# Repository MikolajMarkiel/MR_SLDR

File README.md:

# WARNING!

The project is in build stage. Missing documentation and functionalities will be added in time.

# Overview

The MR_SLDR is a project of remote controlled slider for camera. It will be controlled by Bluetooth Low Energy protocol. The main library source for this project is Zephyr OS.

# How to run

# Software description

## Web_bluetooth

## timer

Due to problems with flexibility occurence of threads in zephyr (minimal period step is 100us) I've decided to leave control of stepper motor up to hardware timer peripheral. Unfortunately right now esp32 timer drivers are dedicated only for counters that lose synchronization after overflow of counted ticks. Because of that I had to add extra modification to counter_esp32_tmr.c file (this file is a driver to handle every action of timer after setting devicetree &timerX status = "okay"). The modification allow us to decide that counter will autoreset after getting alarm or won't. It doesn't harm any project that use old driver, because for this to work user has to add extra `COUNTER_AUTORESET` config to Kconfig file. I've included new counter_esp32_tmr.c file in bin/ directory. The path for replacement is `../zephyrproject/zephyr/drivers/counter/counter_esp32_tmr.c`

## Distance_meter

# Hardware description

## Power section

The main supply for the board is +5V microUSB port. It supplies two DC-DC converters: step-up to +12V and step-down to +3,3V. The +12 DC voltage is needed for charging alternative power supply based on 3 li-ion cells driven by BMS3451 BMS. If there is no USB cable connected, then step-down converter is supplied by +12V instead. There is an external switch that enables step-down converter. If it is disabled, then every peripheral would be powered down except stepper motor driver which would go into sleep mode instead. Connecting USB cable with switch turned off allow charging batteries without turning on the device.
Voltage level of cell block is continually checked by ADC, and the feedback information is given to user via BLE.

## CPU & programming

An ESP32 module has been chosen as a CPU for the device. It has been because of his low cost and support for bluetooth communication and zephyr OS. There are two ways to communicate PC with CPU: via CP2102 USB to UART bridge module connected to micro USB and JTAG connector. Both allow to program flash memory. Additionally the bridge provides serial communication with PC and JTAG give possibility to debug software.

## Stepper motor driver

DRV8825 module has been used as an output driver for stepper motor. It provides easy interface because of it's STEP/DIR functionality. For more information please refer to datasheet of module.

## Distance meter

For checking actual position of camera even after power off the laser distance meter VL53LXX module is connected to CPU by I2C interface. Because it is needed to connect module directly at path of moving camera, then the module has been removed from the main hardware PCB and case. For more information please refer to datasheet of module.

## Camera control blocks

There are also two isolated switches for example for activating remote control of camera or other these types activities. They are designed with use of single channel transoptors PC817.

## EEPROM

The board provides also external EEPROM (M93C76C module) for saving user data of slider settings. It communicates with CPU via SPI interface.

## Mechanicals

The board has been designed for Z57J universal case (https://www.kradex.com.pl/product/enclosures_hermetically_sealed/z57j_ps?lang=en) but it is also possible to print something similar. By now there is no need to provide additional 3D models of case.

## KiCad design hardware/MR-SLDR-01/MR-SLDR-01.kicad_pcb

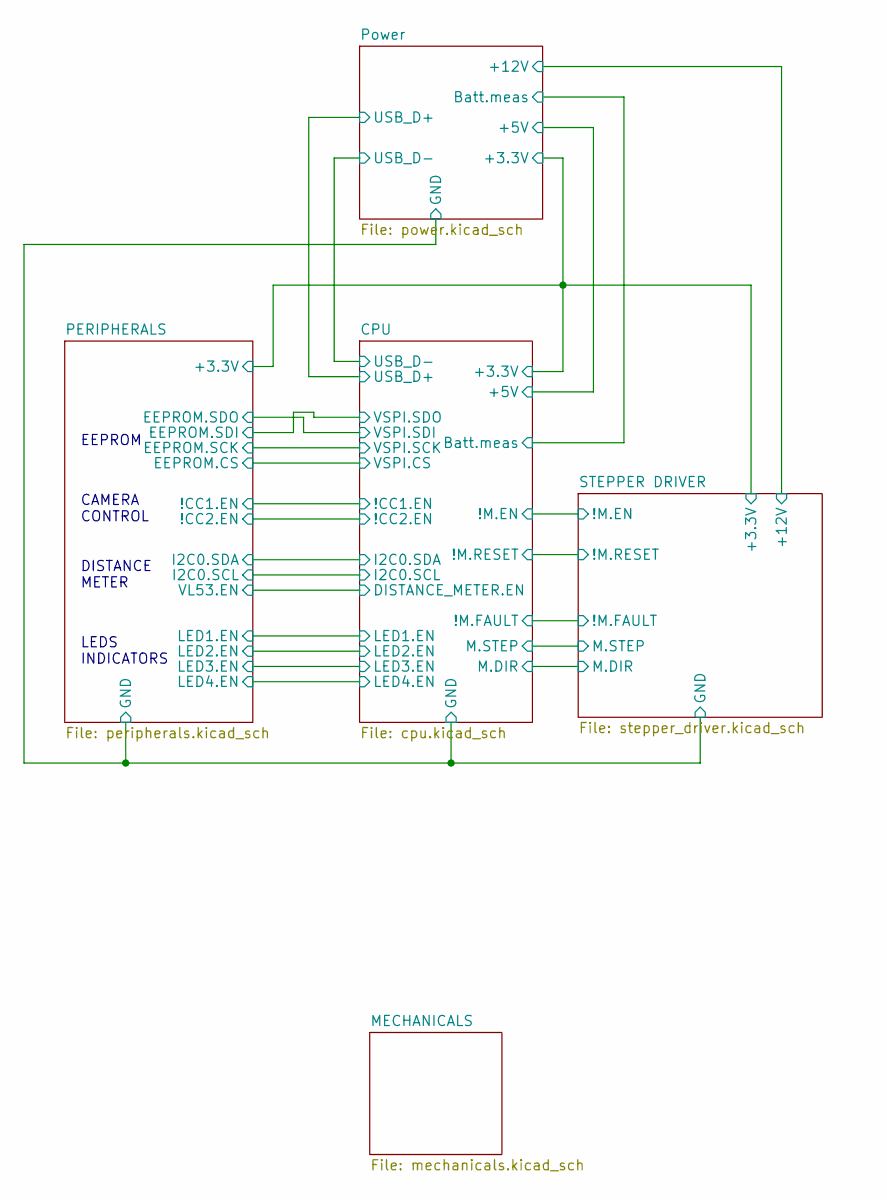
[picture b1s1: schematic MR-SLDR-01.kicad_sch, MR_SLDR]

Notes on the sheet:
LEDS INDICATORS
DISTANCE METER
CAMERA CONTROL
EEPROM

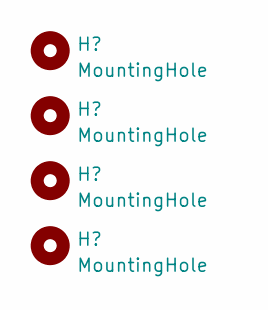
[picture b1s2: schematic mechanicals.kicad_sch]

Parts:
H1, H2, H3, H4: MountingHole; MountingHole_3.2mm_M3

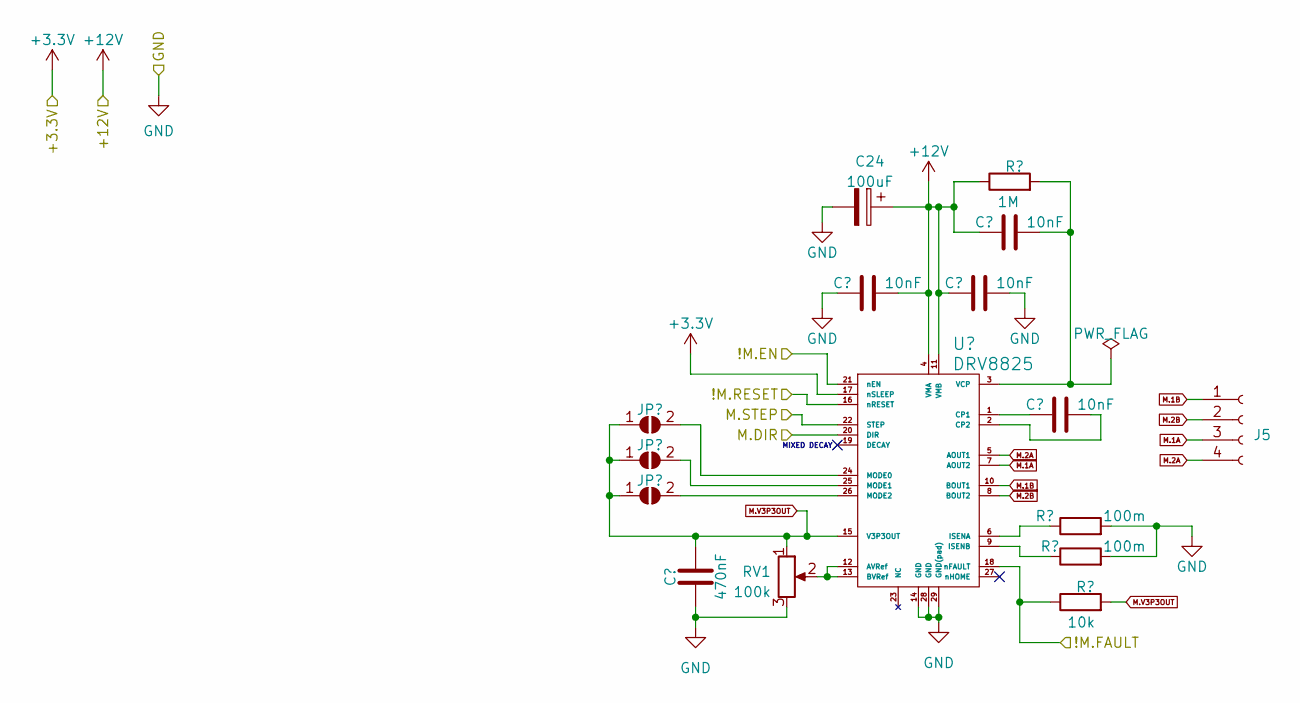
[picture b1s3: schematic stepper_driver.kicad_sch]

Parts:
C23: 470nF; C_0805_2012Metric_Pad1.18x1.45mm_HandSolder
C24: 100uF; CP_Radial_D8.0mm_P3.80mm
C25, C26, C27, C28: 10nF; C_0805_2012Metric_Pad1.18x1.45mm_HandSolder
J5: Conn_01x04_Socket; Molex_KK-254_AE-6410-04A_1x04_P2.54mm_Vertical
JP3, JP4, JP5: SolderJumper_2_Open; SolderJumper-2_P1.3mm_Open_RoundedPad1.0x1.5mm
R35: 1M; R_0805_2012Metric_Pad1.20x1.40mm_HandSolder
R36, R37: 100m; R_1206_3216Metric_Pad1.30x1.75mm_HandSolder
R38: 10k; R_0805_2012Metric_Pad1.20x1.40mm_HandSolder
RV1: 100k; Potentiometer_Bourns_3296W_Vertical
U6: DRV8825; HTSSOP-28-1EP_4.4x9.7mm_P0.65mm_EP3.4x9.5mm_ThermalVias

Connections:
+3.3V: U6.17 (nSLEEP); also elsewhere on the board
+12V: C24.1, C25.2, C26.1, C27.1, R35.1, U6.4 (VMA), U6.11 (VMB); also elsewhere on the board
/CPU/!M.EN: U6.21 (nEN); also elsewhere on the board
/CPU/!M.FAULT: R38.1, U6.18 (nFAULT); also elsewhere on the board
/CPU/!M.RESET: U6.16 (nRESET); also elsewhere on the board
/CPU/M.DIR: U6.20 (DIR); also elsewhere on the board
/CPU/M.STEP: U6.22 (STEP); also elsewhere on the board
GND: C23.1, C24.2, C25.1, C26.2, R36.2, R37.2, RV1.3, U6.14 (GND), U6.28 (GND), U6.29 (GND(pad)); also elsewhere on the board
M.1A: J5.3, U6.7 (AOUT2)
M.1B: J5.1, U6.10 (BOUT1)
M.2A: J5.4, U6.5 (AOUT1)
M.2B: J5.2, U6.8 (BOUT2)
M.V3P3OUT: C23.2, JP3.1 (A), JP4.1 (A), JP5.1 (A), R38.2, RV1.1, U6.15 (V3P3OUT)
unnamed: JP3.2 (B), U6.24 (MODE0)
unnamed: JP4.2 (B), U6.25 (MODE1)
unnamed: JP5.2 (B), U6.26 (MODE2)
unnamed: RV1.2, U6.12 (AVRef), U6.13 (BVRef)
unnamed: C28.1, U6.1 (CP1)
unnamed: C28.2, U6.2 (CP2)
unnamed: R36.1, U6.6 (ISENA)
unnamed: R37.1, U6.9 (ISENB)
unnamed: C27.2, R35.2, U6.3 (VCP)

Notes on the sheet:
MIXED DECAY

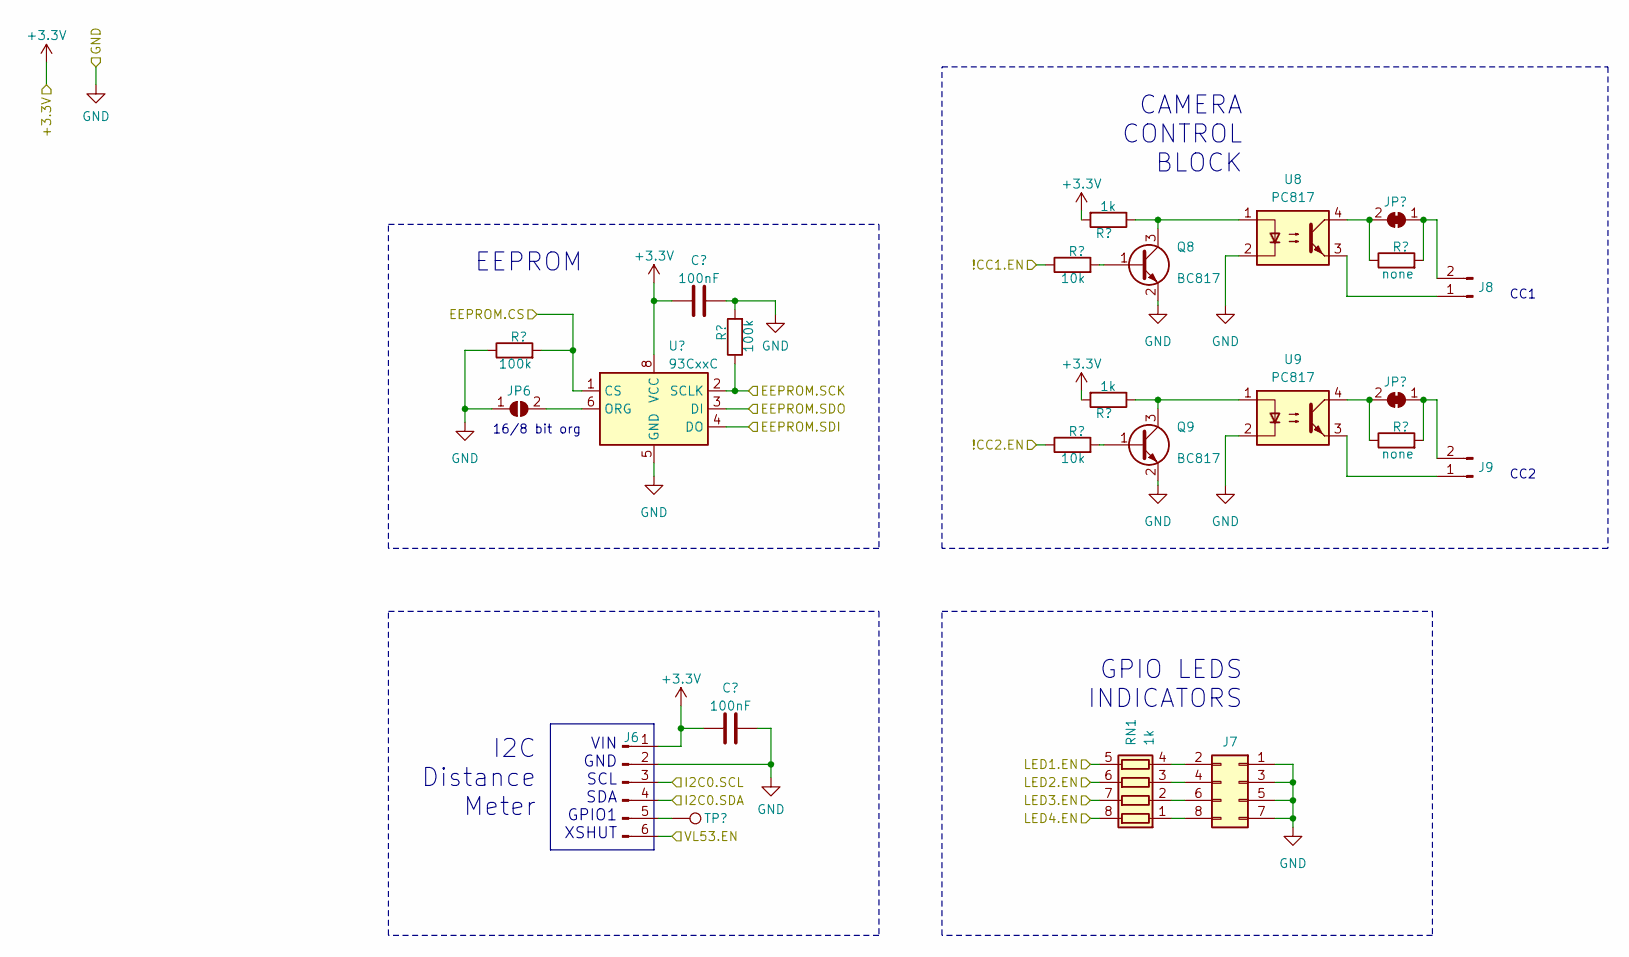
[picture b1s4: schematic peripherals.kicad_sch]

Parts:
C29, C30: 100nF; C_0805_2012Metric_Pad1.18x1.45mm_HandSolder
J6: Conn_01x06_Pin; Molex_KK-254_AE-6410-06A_1x06_P2.54mm_Vertical
J7: Conn_02x04_Odd_Even; PinSocket_2x04_P2.54mm_Vertical
J8, J9: Conn_01x02_Pin; Molex_SL_171971-0002_1x02_P2.54mm_Vertical
JP6: SolderJumper_2_Open; SolderJumper-2_P1.3mm_Open_RoundedPad1.0x1.5mm
JP7, JP8: SolderJumper_2_Bridged; SolderJumper-2_P1.3mm_Bridged_RoundedPad1.0x1.5mm
Q8, Q9: BC817; SOT-23
R39, R40: 100k; R_0805_2012Metric_Pad1.20x1.40mm_HandSolder
R41, R42: 10k; R_0805_2012Metric_Pad1.20x1.40mm_HandSolder
R43, R44: 1k; R_0805_2012Metric_Pad1.20x1.40mm_HandSolder
R45, R46: none; R_0805_2012Metric_Pad1.20x1.40mm_HandSolder
RN1: 1k; R_Array_Convex_4x1206
TP8: TestPoint; TestPoint_THTPad_1.0x1.0mm_Drill0.5mm
U7: 93CxxC; SO-8_3.9x4.9mm_P1.27mm
U8, U9: PC817; DIP-4_W7.62mm

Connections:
+3.3V: C29.2, C30.2, J6.1, R43.2, R44.2, U7.8 (VCC); also elsewhere on the board
/CPU/!CC1.EN: R41.1; also elsewhere on the board
/CPU/!CC2.EN: R42.1; also elsewhere on the board
/CPU/DISTANCE_METER.EN: J6.6; also elsewhere on the board
/CPU/I2C0.SCL: J6.3; also elsewhere on the board
/CPU/I2C0.SDA: J6.4; also elsewhere on the board
/CPU/LED1.EN: RN1.5 (R4.2); also elsewhere on the board
/CPU/LED2.EN: RN1.6 (R3.2); also elsewhere on the board
/CPU/LED3.EN: RN1.7 (R2.2); also elsewhere on the board
/CPU/LED4.EN: RN1.8 (R1.2); also elsewhere on the board
/CPU/VSPI.CS: R39.2, U7.1 (CS); also elsewhere on the board
/CPU/VSPI.SCK: R40.1, U7.2 (SCLK); also elsewhere on the board
/CPU/VSPI.SDI: U7.3 (DI); also elsewhere on the board
/CPU/VSPI.SDO: U7.4 (DO); also elsewhere on the board
GND: C29.1, C30.1, J6.2, J7.1, J7.3, J7.5, J7.7, JP6.1 (A), Q8.2 (E), Q9.2 (E), R39.1, R40.2, U7.5 (GND), U8.2, U9.2; also elsewhere on the board
unnamed: J6.5, TP8.1
unnamed: J7.2, RN1.4 (R4.1)
unnamed: J7.4, RN1.3 (R3.1)
unnamed: J7.6, RN1.2 (R2.1)
unnamed: J7.8, RN1.1 (R1.1)
unnamed: J8.1, U8.3
unnamed: J9.1, U9.3
unnamed: J9.2, JP8.1 (A), R46.2
unnamed: JP6.2 (B), U7.6 (ORG)
unnamed: JP8.2 (B), R46.1, U9.4
unnamed: Q8.1 (B), R41.2
unnamed: Q8.3 (C), R43.1, U8.1
unnamed: Q9.1 (B), R42.2
unnamed: Q9.3 (C), R44.1, U9.1

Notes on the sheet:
CC1
GPIO LEDS INDICATORS
CC2
16/8 bit org
VIN GND SCL SDA GPIO1 XSHUT
I2C Distance Meter
CAMERA CONTROL BLOCK
EEPROM

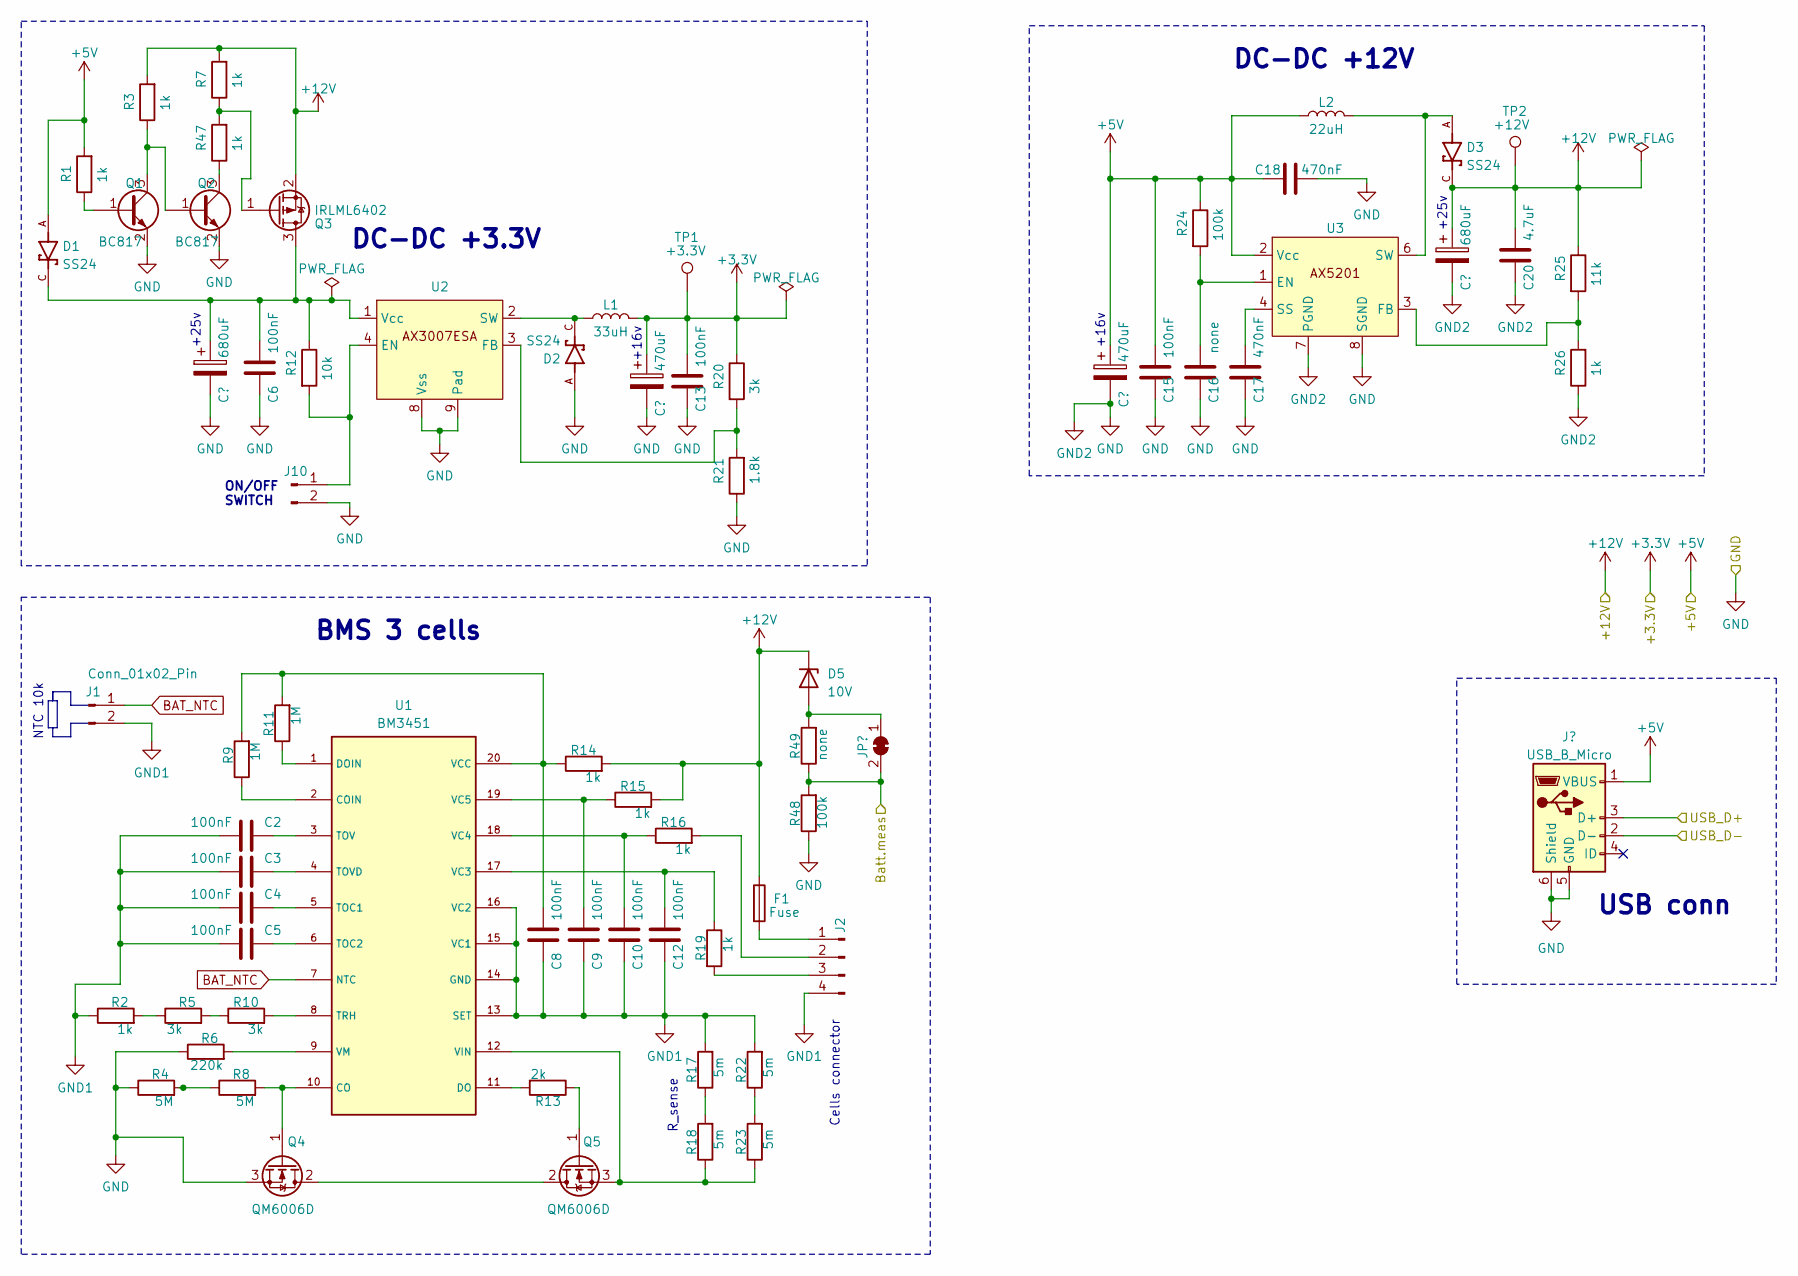
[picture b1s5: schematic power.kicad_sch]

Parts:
C1, C19: 680uF; CP_Radial_D10.0mm_P5.00mm
C2, C3, C4, C5, C6, C8, C9, C10, C12, C13, C15: 100nF; C_0805_2012Metric_Pad1.18x1.45mm_HandSolder
C11, C14: 470uF; CP_Radial_D8.0mm_P3.80mm
C16: none; C_0805_2012Metric_Pad1.18x1.45mm_HandSolder
C17, C18: 470nF; C_0805_2012Metric_Pad1.18x1.45mm_HandSolder
C20: 4.7uF; C_1206_3216Metric_Pad1.33x1.80mm_HandSolder
D1, D2, D3: SS24; DIOM5336X265N; PARTREV 1.1.2
D5: 10V; D_MiniMELF
F1: Fuse; Fuse_1206_3216Metric_Pad1.42x1.75mm_HandSolder
J1, J10: Conn_01x02_Pin; Molex_SL_171971-0002_1x02_P2.54mm_Vertical
J2: Conn_01x04_Pin; Molex_KK-254_AE-6410-04A_1x04_P2.54mm_Vertical
J3: USB_B_Micro; USB_Micro-B_Amphenol_10118194_Horizontal
JP7: SolderJumper_2_Bridged; SolderJumper-2_P1.3mm_Bridged_RoundedPad1.0x1.5mm
L1: 33uH; L_12x12mm_H8mm
L2: 22uH; L_TDK_VLF10040
Q1, Q2: BC817; SOT-23
Q3: IRLML6402; SOT-23
Q4, Q5: QM6006D; TO-252-2
R1, R2, R3, R7, R14, R15, R16, R19, R26, R47: 1k; R_0805_2012Metric_Pad1.20x1.40mm_HandSolder
R4, R8: 5M; R_0805_2012Metric_Pad1.20x1.40mm_HandSolder
R5, R10, R20: 3k; R_0805_2012Metric_Pad1.20x1.40mm_HandSolder
R6: 220k; R_0805_2012Metric_Pad1.20x1.40mm_HandSolder
R9, R11: 1M; R_0805_2012Metric_Pad1.20x1.40mm_HandSolder
R12: 10k; R_0805_2012Metric_Pad1.20x1.40mm_HandSolder
R13: 2k; R_0805_2012Metric_Pad1.20x1.40mm_HandSolder
R17, R18, R22, R23: 5m; R_2512_6332Metric_Pad1.40x3.35mm_HandSolder
R21: 1.8k; R_0805_2012Metric_Pad1.20x1.40mm_HandSolder
R24, R48: 100k; R_0805_2012Metric_Pad1.20x1.40mm_HandSolder
R25: 11k; R_0805_2012Metric_Pad1.20x1.40mm_HandSolder
R49: none; R_0805_2012Metric_Pad1.20x1.40mm_HandSolder
TP1: +3.3V; TestPoint_THTPad_1.0x1.0mm_Drill0.5mm
TP2: +12V; TestPoint_THTPad_1.0x1.0mm_Drill0.5mm
U1: BM3451; TSSOP-20_4.4x6.5mm_P0.65mm
U2, U3: SOIC-8-1EP_3.9x4.9mm_P1.27mm_EP2.29x3mm

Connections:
+3.3V: C11.1, C13.1, L1.2, R20.1, TP1.1; also elsewhere on the board
+5V: C14.1, C15.1, C18.1, D1.A, J3.1 (VBUS), L2.1, R1.2, R24.1, U3.2 (Vcc); also elsewhere on the board
+12V: C19.1, C20.1, D3.C, D5.1 (K), F1.1, Q3.2 (S), R3.2, R7.2, R14.2, R15.2, R25.1, TP2.1; also elsewhere on the board
/CPU/USB_D+: J3.3 (D+); also elsewhere on the board
/CPU/USB_D-: J3.2 (D-); also elsewhere on the board
BAT_NTC: J1.1, U1.7 (NTC)
GND: C1.2, C6.2, C11.2, C13.2, C14.2, C15.2, C16.2, C17.2, C18.2, C19.2, C20.2, D2.A, J3.5 (GND), J3.6 (Shield), J10.2, Q1.2 (E), Q2.2 (E), Q4.3 (S), R4.1, R6.1, R21.1, R26.1, R48.1, U2.5 (Vss), U2.6 (Vss), U2.7 (Vss), U2.8 (Vss), U2.9 (Pad), U3.7 (PGND), U3.8 (SGND); also elsewhere on the board
GND1: C2.1, C3.1, C4.1, C5.1, C8.2, C9.2, C10.2, C12.2, J1.2, J2.4, R2.1, R17.2, R22.2, U1.13 (SET), U1.14 (GND), U1.15 (VC1), U1.16 (VC2)
unnamed: D3.A, L2.2, U3.5 (SW), U3.6 (SW), U3.9 (Pad)
unnamed: F1.2, J2.1
unnamed: J2.2, R16.2
unnamed: J2.3, R19.2
unnamed: J10.1, R12.2, U2.4 (EN)
unnamed: Q1.1 (B), R1.1
unnamed: Q1.3 (C), Q2.1 (B), R3.1
unnamed: Q2.3 (C), R47.1
unnamed: C1.1, C6.1, D1.C, Q3.3 (D), R12.1, U2.1 (Vcc)
unnamed: Q3.1 (G), R7.1, R47.2
unnamed: Q4.2 (D), Q5.2 (D)
unnamed: Q4.1 (G), R8.2, U1.10 (CO)
unnamed: Q5.1 (G), R13.1
unnamed: Q5.3 (S), R18.1, R23.1, U1.12 (VIN)
unnamed: R2.2, R5.1
unnamed: R4.2, R8.1
unnamed: R5.2, R10.1
unnamed: R17.1, R18.2
unnamed: R22.1, R23.2
unnamed: R9.1, U1.2 (COIN)
unnamed: R13.2, U1.11 (DO)
unnamed: R11.1, U1.1 (DOIN)
unnamed: C4.2, U1.5 (TOC1)
unnamed: C5.2, U1.6 (TOC2)
unnamed: C2.2, U1.3 (TOV)
unnamed: C3.2, U1.4 (TOVD)
unnamed: R10.2, U1.8 (TRH)
unnamed: C12.1, R19.1, U1.17 (VC3)
unnamed: C10.1, R16.1, U1.18 (VC4)
unnamed: C9.1, R15.1, U1.19 (VC5)
unnamed: C8.1, R9.2, R11.2, R14.1, U1.20 (VCC)
unnamed: R6.2, U1.9 (VM)
unnamed: R20.2, R21.2, U2.3 (FB)
unnamed: D2.C, L1.1, U2.2 (SW)
unnamed: C16.1, R24.2, U3.1 (EN)
unnamed: R25.2, R26.2, U3.3 (FB)
unnamed: C17.1, U3.4 (SS)

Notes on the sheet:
USB conn
+25v
R_sense
BMS 3 cells
DC-DC +12V
+16v
ON/OFF SWITCH
NTC 10k
DC-DC +3.3V
Cells connector

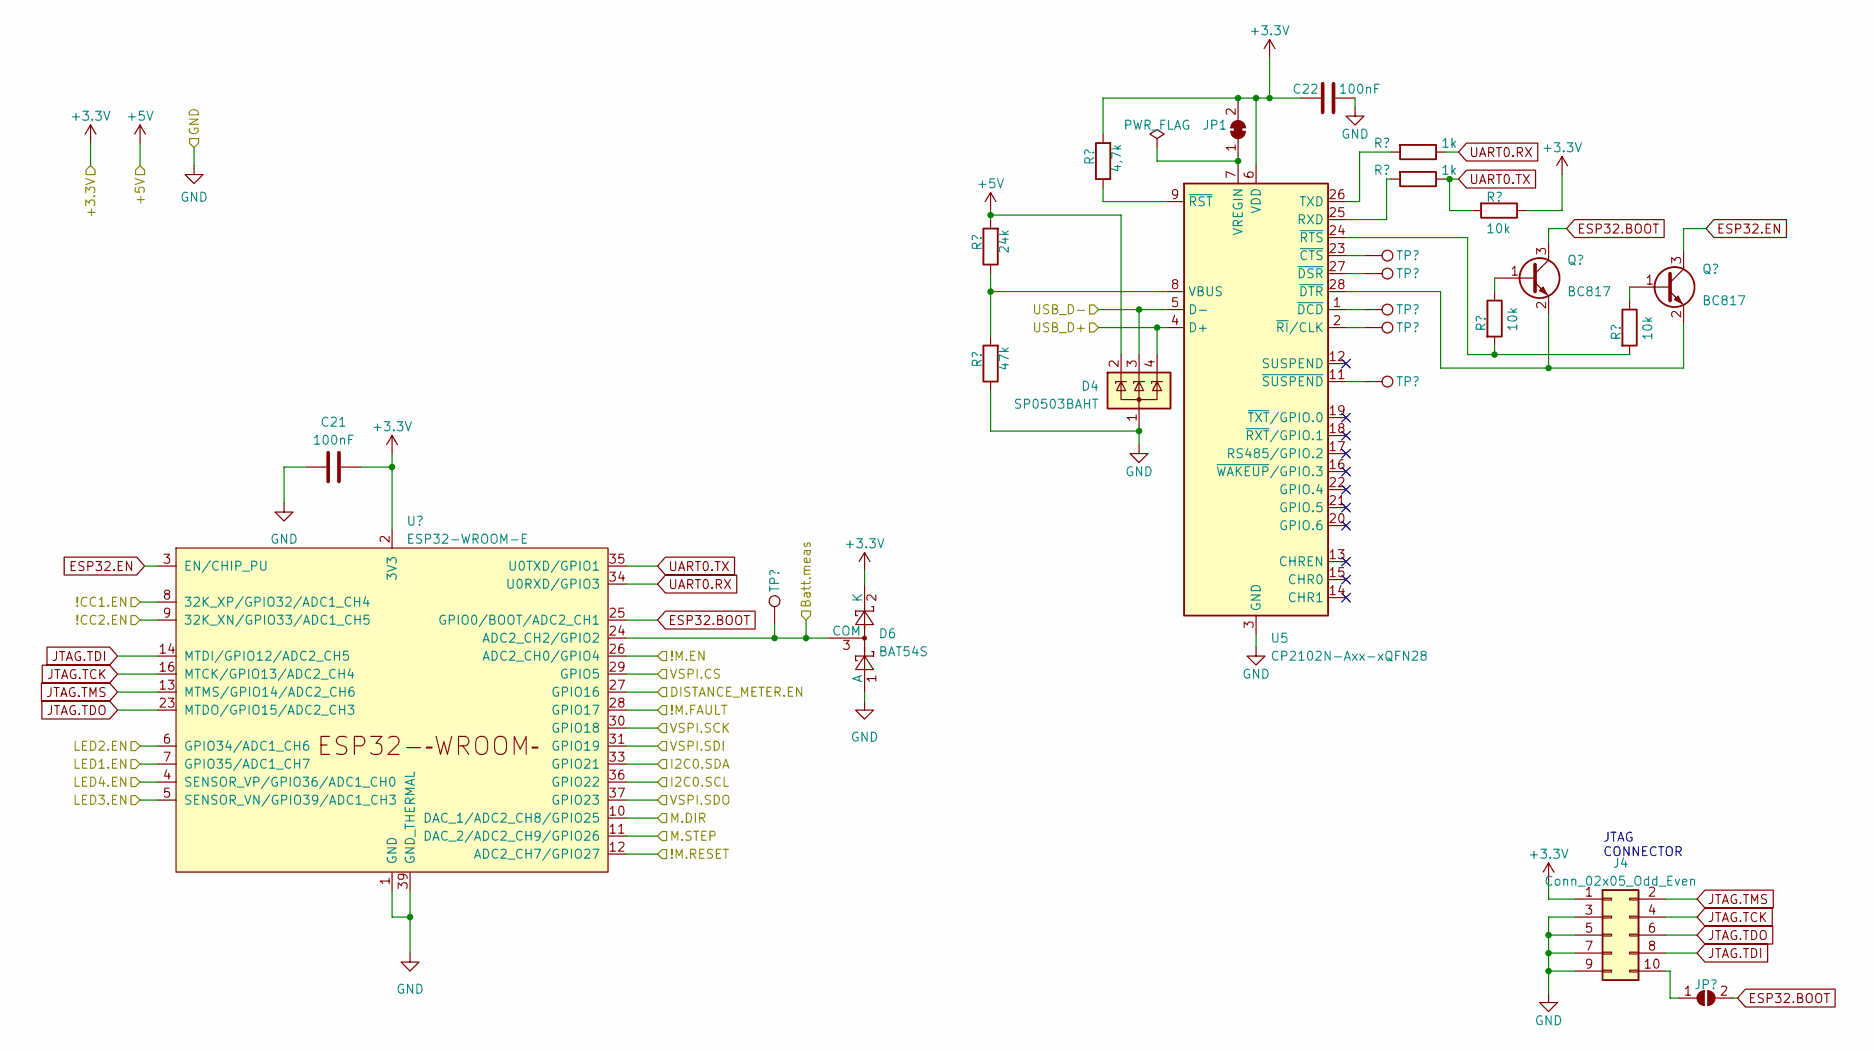
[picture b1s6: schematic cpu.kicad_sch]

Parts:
Batt.meas1: TestPoint; TestPoint_THTPad_1.0x1.0mm_Drill0.5mm
C21, C22: 100nF; C_0805_2012Metric_Pad1.18x1.45mm_HandSolder
D4: SP0503BAHT; SOT-143
D6: BAT54S; SOT-23
J4: Conn_02x05_Odd_Even; PinHeader_2x05_P2.00mm_Vertical
JP1: SolderJumper_2_Bridged; SolderJumper-2_P1.3mm_Bridged_RoundedPad1.0x1.5mm
JP2: SolderJumper_2_Open; SolderJumper-2_P1.3mm_Open_RoundedPad1.0x1.5mm
Q6, Q7: BC817; SOT-23
R27: 24k; R_0805_2012Metric_Pad1.20x1.40mm_HandSolder
R28: 47k; R_0805_2012Metric_Pad1.20x1.40mm_HandSolder
R29: 4,7k; R_0805_2012Metric_Pad1.20x1.40mm_HandSolder
R30, R31: 1k; R_0805_2012Metric_Pad1.20x1.40mm_HandSolder
R32, R33, R34: 10k; R_0805_2012Metric_Pad1.20x1.40mm_HandSolder
TP3, TP4, TP5, TP6, TP7: TestPoint; TestPoint_THTPad_1.0x1.0mm_Drill0.5mm
U4: ESP32-WROOM-E; ESP32-WROOM-32E
U5: CP2102N-Axx-xQFN28; QFN-28-1EP_5x5mm_P0.5mm_EP3.35x3.35mm

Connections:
+3.3V: C21.2, C22.1, D6.2 (K), J4.1, JP1.2 (B), R29.2, R33.1, U4.2 (3V3), U5.6 (VDD); also elsewhere on the board
+5V: D4.2 (K), R27.2; also elsewhere on the board
/CPU/!CC1.EN: U4.8 (32K_XP/GPIO32/ADC1_CH4); also elsewhere on the board
/CPU/!CC2.EN: U4.9 (32K_XN/GPIO33/ADC1_CH5); also elsewhere on the board
/CPU/!M.EN: U4.26 (ADC2_CH0/GPIO4); also elsewhere on the board
/CPU/!M.FAULT: U4.28 (GPIO17); also elsewhere on the board
/CPU/!M.RESET: U4.12 (ADC2_CH7/GPIO27); also elsewhere on the board
/CPU/DISTANCE_METER.EN: U4.27 (GPIO16); also elsewhere on the board
/CPU/I2C0.SCL: U4.36 (GPIO22); also elsewhere on the board
/CPU/I2C0.SDA: U4.33 (GPIO21); also elsewhere on the board
/CPU/LED1.EN: U4.7 (GPIO35/ADC1_CH7); also elsewhere on the board
/CPU/LED2.EN: U4.6 (GPIO34/ADC1_CH6); also elsewhere on the board
/CPU/LED3.EN: U4.5 (SENSOR_VN/GPIO39/ADC1_CH3); also elsewhere on the board
/CPU/LED4.EN: U4.4 (SENSOR_VP/GPIO36/ADC1_CH0); also elsewhere on the board
/CPU/M.DIR: U4.10 (DAC_1/ADC2_CH8/GPIO25); also elsewhere on the board
/CPU/M.STEP: U4.11 (DAC_2/ADC2_CH9/GPIO26); also elsewhere on the board
/CPU/USB_D+: D4.4 (K), U5.4 (D+); also elsewhere on the board
/CPU/USB_D-: D4.3 (K), U5.5 (D-); also elsewhere on the board
/CPU/VSPI.CS: U4.29 (GPIO5); also elsewhere on the board
/CPU/VSPI.SCK: U4.30 (GPIO18); also elsewhere on the board
/CPU/VSPI.SDI: U4.31 (GPIO19); also elsewhere on the board
/CPU/VSPI.SDO: U4.37 (GPIO23); also elsewhere on the board
ESP32.BOOT: JP2.2 (B), Q6.3 (C), U4.25 (GPIO0/BOOT/ADC2_CH1)
ESP32.EN: Q7.3 (C), U4.3 (EN/CHIP_PU)
GND: C21.1, C22.2, D4.1 (A), D6.1 (A), J4.3, J4.5, J4.7, J4.9, R28.1, U4.1 (GND), U4.15 (GND), U4.38 (GND), U4.39 (GND_THERMAL), U5.3 (GND), U5.29 (GND); also elsewhere on the board
JTAG.TCK: J4.4, U4.16 (MTCK/GPIO13/ADC2_CH4)
JTAG.TDI: J4.8, U4.14 (MTDI/GPIO12/ADC2_CH5)
JTAG.TDO: J4.6, U4.23 (MTDO/GPIO15/ADC2_CH3)
JTAG.TMS: J4.2, U4.13 (MTMS/GPIO14/ADC2_CH6)
unnamed: J4.10, JP2.1 (A)
unnamed: JP1.1 (A), U5.7 (VREGIN)
unnamed: Q6.1 (B), R32.1
unnamed: Q6.2 (E), Q7.2 (E), U5.28 (~DTR)
unnamed: Q7.1 (B), R34.1
unnamed: R31.2, U5.25 (RXD)
unnamed: R30.2, U5.26 (TXD)
unnamed: R27.1, R28.2, U5.8 (VBUS)
unnamed: TP3.1, U5.23 (~CTS)
unnamed: TP5.1, U5.1 (~DCD)
unnamed: TP4.1, U5.27 (~DSR)
unnamed: TP6.1, U5.2 (~RI/CLK)
unnamed: R29.1, U5.9 (~RST)
unnamed: R32.2, R34.2, U5.24 (~RTS)
unnamed: TP7.1, U5.11 (~SUSPEND)
UART0.RX: R30.1, U4.34 (U0RXD/GPIO3)
UART0.TX: R31.1, R33.2, U4.35 (U0TXD/GPIO1)

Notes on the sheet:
JTAG CONNECTOR

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
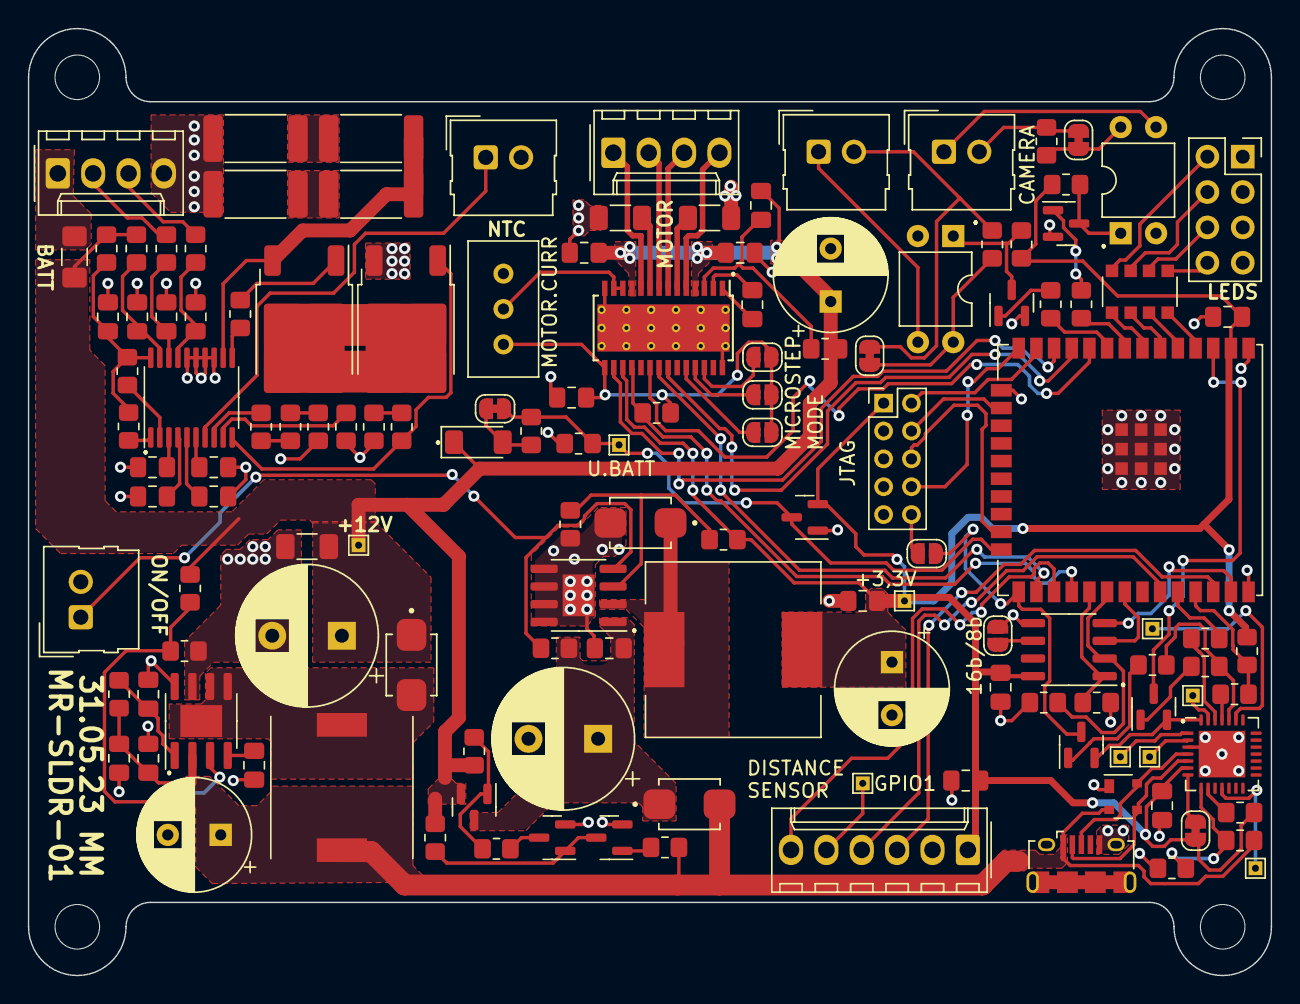
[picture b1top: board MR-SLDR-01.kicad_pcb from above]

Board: 2 copper layers, 89.3 x 68.0 mm, 139 parts (0 on the bottom side), 118 nets.

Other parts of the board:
JP9: SolderJumper_2_Bridged; SolderJumper-2_P1.3mm_Bridged_RoundedPad1.0x1.5mm

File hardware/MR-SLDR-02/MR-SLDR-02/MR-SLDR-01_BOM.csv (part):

"Source:","/home/mikolaj/projects/MR-SLDR/hardware/MR-SLDR-01/MR-SLDR-01.kicad_sch"
"Date:","pią, 2 cze 2023, 03:15:36"
"Tool:","Eeschema 7.0.2-6a45011f42~172~ubuntu22.04.1"
"Generator:","/usr/share/kicad/plugins/bom_csv_grouped_by_value.py"
"Component Count:","139"

"Collated Components:"

"Item","Qty","Reference(s)","Value","LibPart","Footprint","Datasheet","DNP","MANUFACTURER","MAXIMUM_PACKAGE_HEIGHT","PARTREV","STANDARD","Sim.Device","Sim.Pins","Sim.Type"
"1","7","Batt.meas1, TP3, TP4, TP5, TP6, TP7, TP8","TestPoint","Connector:TestPoint","TestPoint:TestPoint_THTPad_1.0x1.0mm_Drill0.5mm","~","","","","","","","",""
"2","2","C1, C19","680uF","Device:C_Polarized","Capacitor_THT:CP_Radial_D10.0mm_P5.00mm","~","","","","","","","",""
"3","15","C2, C3, C4, C5, C6, C8, C9, C10, C12, C13, C15, C21, C22, C29, C30","100nF","Device:C","Capacitor_SMD:C_0805_2012Metric_Pad1.18x1.45mm_HandSolder","~","","","","","","","",""
"4","2","C11, C14","470uF","Device:C_Polarized","Capacitor_THT:CP_Radial_D8.0mm_P3.80mm","~","","","","","","","",""
"5","1","C16","none","Device:C","Capacitor_SMD:C_0805_2012Metric_Pad1.18x1.45mm_HandSolder","~","","","","","","","",""
"6","3","C17, C18, C23","470nF","Device:C","Capacitor_SMD:C_0805_2012Metric_Pad1.18x1.45mm_HandSolder","~","","","","","","","",""
"7","1","C20","4.7uF","Device:C","Capacitor_SMD:C_1206_3216Metric_Pad1.33x1.80mm_HandSolder","~","","","","","","","",""
"8","1","C24","100uF","Device:C_Polarized","Capacitor_THT:CP_Radial_D8.0mm_P3.80mm","~","","","","","","","",""
"9","4","C25, C26, C27, C28","10nF","Device:C","Capacitor_SMD:C_0805_2012Metric_Pad1.18x1.45mm_HandSolder","~","","","","","","","",""
"10","3","D1, D2, D3","SS24","SS24:SS24","bin:DIOM5336X265N","","","ON Semiconductor","2.65 mm","1.1.2","IPC 7351B","","",""
"11","1","D4","SP0503BAHT","Power_Protection:SP0503BAHT","Package_TO_SOT_SMD:SOT-143","http://www.littelfuse.com/~/media/files/littelfuse/technical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","","","","","","","",""
"12","1","D5","10V","Device:D_Zener","Diode_SMD:D_MiniMELF","~","","","","","","","",""
"13","1","D6","BAT54S","Diode:BAT54S","Package_TO_SOT_SMD:SOT-23","https://www.diodes.com/assets/Datasheets/ds11005.pdf","","","","","","","",""
"14","1","F1","Fuse","Device:Fuse","Fuse:Fuse_1206_3216Metric_Pad1.42x1.75mm_HandSolder","~","","","","","","","",""
"15","4","H1, H2, H3, H4","MountingHole","Mechanical:MountingHole","MountingHole:MountingHole_3.2mm_M3","~","","","","","","","",""
"16","4","J1, J8, J9, J10","Conn_01x02_Pin","Connector:Conn_01x02_Pin","Connector_Molex:Molex_SL_171971-0002_1x02_P2.54mm_Vertical","~","","","","","","","",""
"17","1","J2","Conn_01x04_Pin","Connector:Conn_01x04_Pin","Connector_Molex:Molex_KK-254_AE-6410-04A_1x04_P2.54mm_Vertical","~","","","","","","","",""
"18","1","J3","USB_B_Micro","Connector:USB_B_Micro","Connector_USB:USB_Micro-B_Amphenol_10118194_Horizontal","~","","","","","","","",""
"19","1","J4","Conn_02x05_Odd_Even","Connector_Generic:Conn_02x05_Odd_Even","Connector_PinHeader_2.00mm:PinHeader_2x05_P2.00mm_Vertical","~","","","","","","","",""
"20","1","J5","Conn_01x04_Socket","Connector:Conn_01x04_Socket","Connector_Molex:Molex_KK-254_AE-6410-04A_1x04_P2.54mm_Vertical","~","","","","","","","",""
"21","1","J6","Conn_01x06_Pin","Connector:Conn_01x06_Pin","Connector_Molex:Molex_KK-254_AE-6410-06A_1x06_P2.54mm_Vertical","~","","","","","","","",""
"22","1","J7","Conn_02x04_Odd_Even","Connector_Generic:Conn_02x04_Odd_Even","Connector_PinSocket_2.54mm:PinSocket_2x04_P2.54mm_Vertical","~","","","","","","","",""
"23","4","JP1, JP7, JP8, JP9","SolderJumper_2_Bridged","Jumper:SolderJumper_2_Bridged","Jumper:SolderJumper-2_P1.3mm_Bridged_RoundedPad1.0x1.5mm","~","","","","","","","",""
"24","5","JP2, JP3, JP4, JP5, JP6","SolderJumper_2_Open","Jumper:SolderJumper_2_Open","Jumper:SolderJumper-2_P1.3mm_Open_RoundedPad1.0x1.5mm","~","","","","","","","",""
"25","1","L1","33uH","Device:L","Inductor_SMD:L_12x12mm_H8mm","~","","","","","","","",""
"26","1","L2","22uH","Device:L","Inductor_SMD:L_TDK_VLF10040","~","","","","","","","",""
"27","6","Q1, Q2, Q6, Q7, Q8, Q9","BC817","Transistor_BJT:BC817","Package_TO_SOT_SMD:SOT-23","https://www.onsemi.com/pub/Collateral/BC818-D.pdf","","","","","","","",""
"28","1","Q3","IRLML6402","Transistor_FET:IRLML6402","Package_TO_SOT_SMD:SOT-23","https://www.infineon.com/dgdl/irlml6402pbf.pdf?fileId=5546d4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","","","","","","","",""
"29","2","Q4, Q5","QM6006D","Transistor_FET:QM6006D","Package_TO_SOT_SMD:TO-252-2","http://www.jaolen.com/images/pdf/QM6006D.pdf","","","","","","NMOS","1=D 2=G 3=S","VDMOS"
"30","14","R1, R2, R3, R7, R14, R15, R16, R19, R26, R30, R31, R43, R44, R47","1k","Device:R","Resistor_SMD:R_0805_2012Metric_Pad1.20x1.40mm_HandSolder","~","","","","","","","",""
"31","2","R4, R8","5M","Device:R","Resistor_SMD:R_0805_2012Metric_Pad1.20x1.40mm_HandSolder","~","","","","","","","",""
"32","3","R5, R10, R20","3k","Device:R","Resistor_SMD:R_0805_2012Metric_Pad1.20x1.40mm_HandSolder","~","","","","","","","",""
"33","1","R6","220k","Device:R","Resistor_SMD:R_0805_2012Metric_Pad1.20x1.40mm_HandSolder","~","","","","","","","",""
"34","3","R9, R11, R35","1M","Device:R","Resistor_SMD:R_0805_2012Metric_Pad1.20x1.40mm_HandSolder","~","","","","","","","",""
"35","7","R12, R32, R33, R34, R38, R41, R42","10k","Device:R","Resistor_SMD:R_0805_2012Metric_Pad1.20x1.40mm_HandSolder","~","","","","","","","",""
"36","1","R13","2k","Device:R","Resistor_SMD:R_0805_2012Metric_Pad1.20x1.40mm_HandSolder","~","","","","","","","",""
"37","4","R17, R18, R22, R23","5m","Device:R","Resistor_SMD:R_2512_6332Metric_Pad1.40x3.35mm_HandSolder","~","","","","","","","",""
"38","1","R21","1.8k","Device:R","Resistor_SMD:R_0805_2012Metric_Pad1.20x1.40mm_HandSolder","~","","","","","","","",""
"39","4","R24, R39, R40, R48","100k","Device:R","Resistor_SMD:R_0805_2012Metric_Pad1.20x1.40mm_HandSolder","~","","","","","","","",""
"40","1","R25","11k","Device:R","Resistor_SMD:R_0805_2012Metric_Pad1.20x1.40mm_HandSolder","~","","","","","","","",""
"41","1","R27","24k","Device:R","Resistor_SMD:R_0805_2012Metric_Pad1.20x1.40mm_HandSolder","~","","","","","","","",""
"42","1","R28","47k","Device:R","Resistor_SMD:R_0805_2012Metric_Pad1.20x1.40mm_HandSolder","~","","","","","","","",""
"43","1","R29","4,7k","Device:R","Resistor_SMD:R_0805_2012Metric_Pad1.20x1.40mm_HandSolder","~","","","","","","","",""
"44","2","R36, R37","100m","Device:R","Resistor_SMD:R_1206_3216Metric_Pad1.30x1.75mm_HandSolder","~","","","","","","","",""
"45","3","R45, R46, R49","none","Device:R","Resistor_SMD:R_0805_2012Metric_Pad1.20x1.40mm_HandSolder","~","","","","","","","",""
"46","1","RN1","1k","Device:R_Pack04","Resistor_SMD:R_Array_Convex_4x1206","~","","","","","","","",""
"47","1","RV1","100k","Device:R_Potentiometer","Potentiometer_THT:Potentiometer_Bourns_3296W_Vertical","~","","","","","","","",""
"48","1","TP1","+3.3V","Connector:TestPoint","TestPoint:TestPoint_THTPad_1.0x1.0mm_Drill0.5mm","~","","","","","","","",""
"49","1","TP2","+12V","Connector:TestPoint","TestPoint:TestPoint_THTPad_1.0x1.0mm_Drill0.5mm","~","","","","","","","",""
"50","1","U1","BM3451","BM3451:BM3451(20pin)","Package_SO:TSSOP-20_4.4x6.5mm_P0.65mm","","","","","","","","",""
"51","1","U2","~","axelite:AX3007ESA","Package_SO:SOIC-8-1EP_3.9x4.9mm_P1.27mm_EP2.29x3mm","","","","","","","","",""
"52","1","U3","~","axelite:AX5201","Package_SO:SOIC-8-1EP_3.9x4.9mm_P1.27mm_EP2.29x3mm","","","","","","","","",""
"53","1","U4","ESP32-WROOM-E","Espressif:ESP32-WROOM-E","Espressif:ESP32-WROOM-32E","https://www.espressif.com/sites/default/files/documentation/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","","","","","","","",""
"54","1","U5","CP2102N-Axx-xQFN28","Interface_USB:CP2102N-Axx-xQFN28","Package_DFN_QFN:QFN-28-1EP_5x5mm_P0.5mm_EP3.35x3.35mm","https://www.silabs.com/documents/public/data-sheets/cp2102n-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","","","","","","","",""
"55","1","U6","DRV8825","DRV8825:DRV8825","Package_SO:HTSSOP-28-1EP_4.4x9.7mm_P0.65mm_EP3.4x9.5mm_ThermalVias","","","","","","","","",""
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
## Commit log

2023-04-27 v0.1 Initial version
2023-05-08 v0.2 - switch to hardware timer peripheral, modified counter_esp32_tmr.c driver, reorganize repositorium
2023-05-13 v0.3 slider thread config correction
2023-05-13 v0.4 added interval feature to c code
2023-05-13 v0.5 added stepper motor soft start feature
2023-05-15 v0.6 added soft start & intervals to interface and some code corrections
2023-05-16 added hardware concept
2023-05-16 v0.7 reorder code
2023-06-02 finalized hardware design MR-SLDR-01
2023-06-02 removed backups
2023-06-07 v0.8 MM added rangefinder; move bt handler from main.c to slider_bt.c
2023-06-19 added prototype of calibration procedure
2023-06-19 fixed differences between BT notify and BT read procedures
2023-06-19 new concept of interface
2023-06-20 fixed updating css style during script execution
2023-06-20 fixed communication, maintained connection, check if device is disconnected
2024-08-25 old_changes_bp
2024-08-25 old_changes_bp2
2024-08-25 recent updates
2024-09-01 added custom boards & cmake presets
2024-09-02 add compile_commands.json
2024-09-02 build mr_sldr_01 target
2024-09-02 remove useless config in custom board
2024-09-02 workaround for espressif monitor
2024-09-21 rebuild stepper library
2024-09-21 fix issues with LED gpios
2024-09-21 updated main
2024-09-21 update changes with fixes for next PCB iteration
2024-09-21 move led test function to its module
2024-09-22 fixed motor soft start during intervals
2024-09-23 add get & update slider config
2024-09-23 temp run slider_bt module
2024-10-27 refactor slider_bt module
2024-11-13 fix cmd_handler
2024-11-23 add alpha tests
